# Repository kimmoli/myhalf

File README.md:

MYHALF v1.10
======

Otherhalf breakout board for Jolla

Bill of materials

R1, R2  0603 2k15 (or 2k2) I2C 3.3V pullups. I usually use 2k15 from E96 series.

R3      0603 330 ohms or something like that for led series resistor

C1, C2  0603 1µF 16V X7R

H1      0603 Led of your favorite colour (for blue or white, change R3)

N1      MCP1700-1802E (Microchip) in SOT23 1.8V Regulator

D1      PCA9517DGKR (TI) in MSOP8 (or PCA9517DP (NXP) in TSSOP-8) I2C Level translator
        http://www.nxp.com/documents/data_sheet/PCA9517.pdf
        
D3      AT24C02D-STUM-T (Atmel) in SOT23-5 I2C EEPROM 2kbit
        http://www.atmel.com/Images/Atmel-8871-SEEPROM-AT24C01D-02D-Datasheet.pdf
        
X1      2.54mm (0.1") pinheader 10 pins, or just solder wires

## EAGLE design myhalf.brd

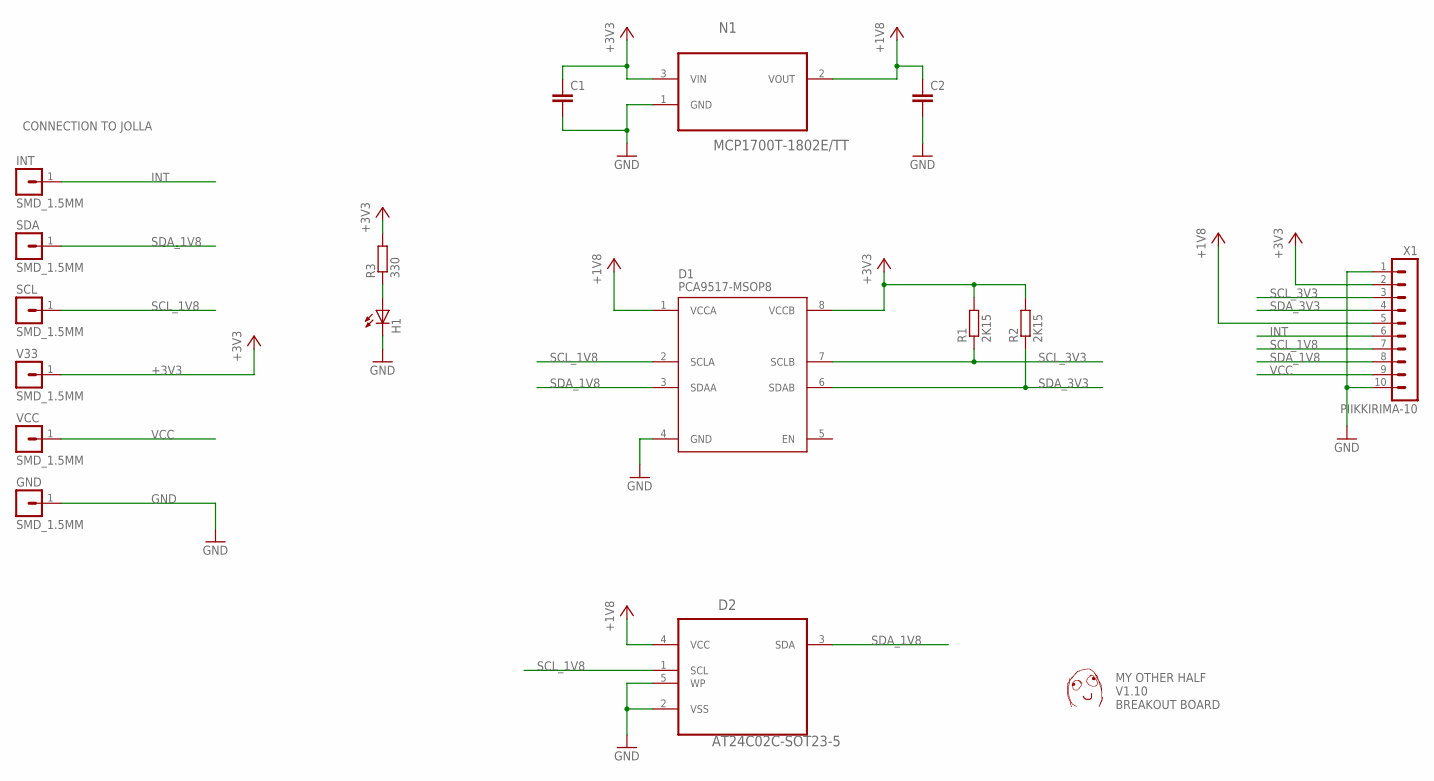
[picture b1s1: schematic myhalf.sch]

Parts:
C1, C2: C-EUC0603; C0603
D1: PCA9517-MSOP8; SOP65P490X110-8N
D2: AT24C02C-SOT23-5; SOT95P280X145-5N
GND: SMD_1.5MM; SMD_ROUND_1.5MM
H1: LEDCHIP-LED0603; CHIP-LED0603
INT: SMD_1.5MM; SMD_ROUND_1.5MM
N1: MCP1700T-1802E/TT; SOT95P237X112-3N
R1, R2: 2K15; R0603
R3: 330; R0603
SCL: SMD_1.5MM; SMD_ROUND_1.5MM
SDA: SMD_1.5MM; SMD_ROUND_1.5MM
U$1: DAFUG
V33: SMD_1.5MM; SMD_ROUND_1.5MM
VCC: SMD_1.5MM; SMD_ROUND_1.5MM
X1: PIIKKIRIMA-10

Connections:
+1V8: C2.1, D1.1 (VCCA), D2.4 (VCC), N1.2 (VOUT), X1.5
+3V3: C1.1, D1.8 (VCCB), N1.3 (VIN), R1.2, R2.2, R3.2, V33.1, X1.2
GND: C1.2, C2.2, D1.4 (GND), D2.2 (VSS), D2.5 (WP), GND.1, H1.C, N1.1 (GND), X1.1, X1.10
INT: INT.1, X1.6
unnamed: H1.A, R3.1
SCL_1V8: D1.2 (SCLA), D2.1 (SCL), SCL.1, X1.7
SCL_3V3: D1.7 (SCLB), R1.1, X1.3
SDA_1V8: D1.3 (SDAA), D2.3 (SDA), SDA.1, X1.8
SDA_3V3: D1.6 (SDAB), R2.1, X1.4
VCC: VCC.1, X1.9

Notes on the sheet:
MY OTHER HALF V1.10 BREAKOUT BOARD
CONNECTION TO JOLLA

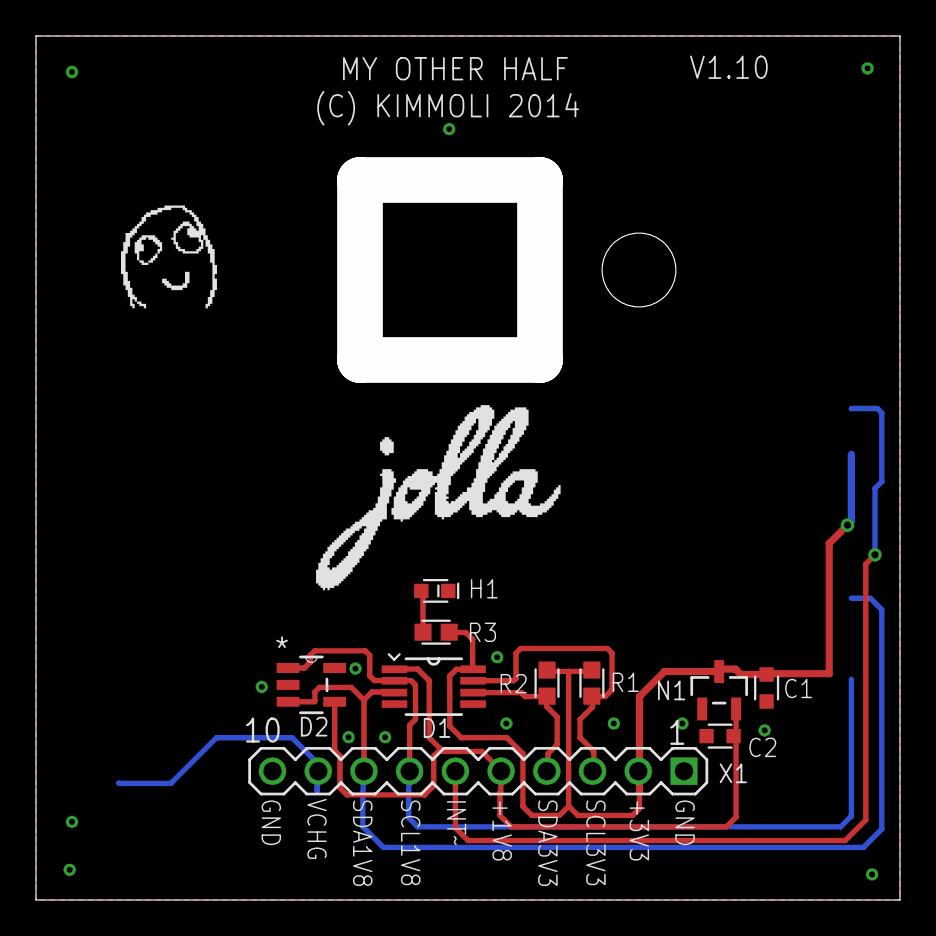
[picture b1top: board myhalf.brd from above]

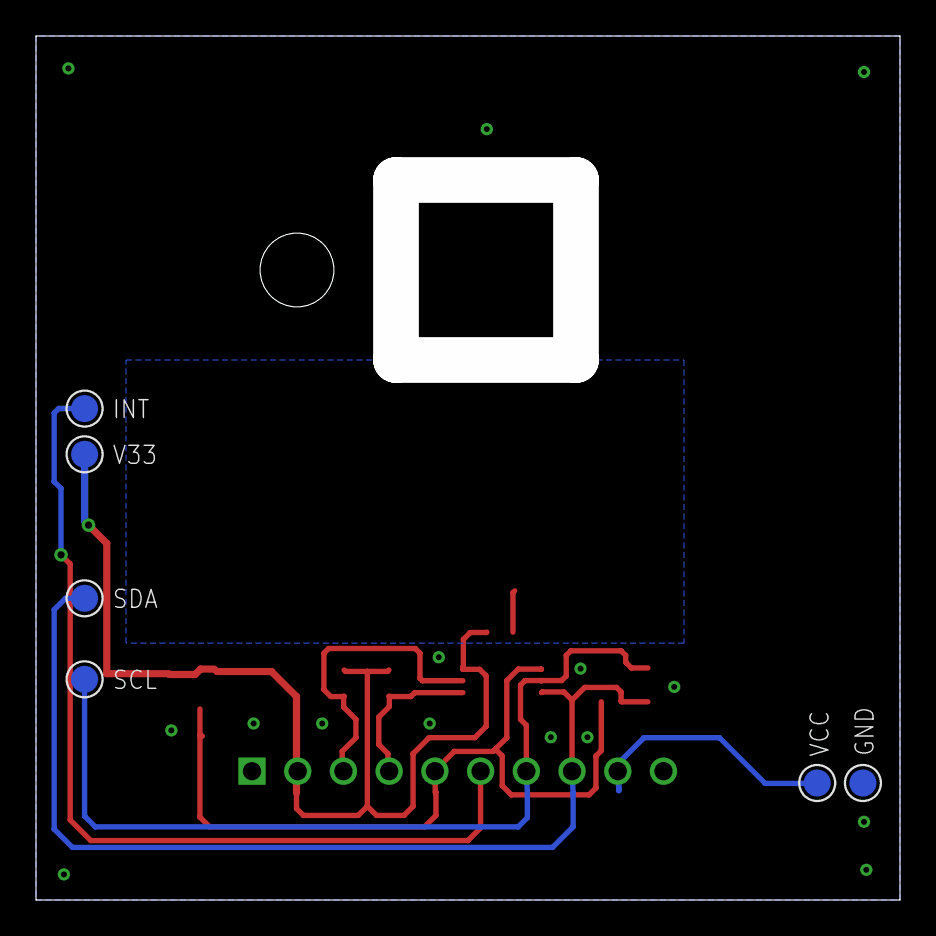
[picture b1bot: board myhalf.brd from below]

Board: 2 copper layers, 48.0 x 48.0 mm, 18 parts (6 on the bottom side), 10 nets.

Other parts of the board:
U$2: JOLLALOGO

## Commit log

2013-12-13 initial
2013-12-14 pogo-mating pads placed, outline drawn
2013-12-14 some more work progress...
2013-12-14 good night
2013-12-16 V1.00
2014-01-27 v1.10
2014-02-20 Clip STL for 0.8mm pcb added
2014-02-25 Clip modified, clearance to antennas
